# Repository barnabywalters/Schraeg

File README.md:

# Schräg

Schräg is an 8HP multimode filter module for the eurorack format, based off the [Bastl Cinnamon](https://bastl-instruments.com/eurorack/modules/cinnamon).

## Smaller Warning and Disclaimer

As of 2021-03-01, at least one person has reported successfully building the current board revision. However, another builder reported a minor issue with the attenuverter circuits which prevents full-range voltage control over resonance (and limits voltage control over FM). This should be fixable only with component substitutions, we’re working on a fix. More information and updates [in the corresponding lines thread](https://llllllll.co/t/diy-module-release-schrag-bastl-cinnamon-rework/40590).

See the Changelog below for more updates and version-specific fixes.

## Quick links

* [Schematic](Schraeg/Schraeg.pdf)
* [Gerbers](Schraeg/output)
* [BOM](Schraeg/Schraeg%20BOM.csv)
* [Schräg on ModularGrid](https://www.modulargrid.net/e/other-unknown-schraeg)
* [Schräg release and Q&A thread on lines](https://llllllll.co/t/diy-module-release-schrag-bastl-cinnamon-rework/40590)

## Need help assembling your Schräg?

I can’t promise quick responses, but am happy to try to help out!

If you’re **having trouble or need help assembling or troubleshooting** a Schräg, please start a [discussion](https://github.com/barnabywalters/Schraeg/discussions/new).

If you’ve **found a specific error which needs fixing**, please file an [issue](https://github.com/barnabywalters/Schraeg/issues/new).

If you’re not sure which, start a discussion, and we’ll convert it into an issue if we can distill it into a concrete problem.

## Features

Schräg is effectively a repackaged Bastl Cinnamon:

* Multimode filter with independent outputs (2-pole LP, 2-pole HP, 1-pole BP)
* V/oct input
* Self-resonates for use as a sine oscillator
* Input with an attenuator and 5x gain switch
* Two character switches for altering the resonance tracking
* All-SMD construction in a DIY-friendly format, with 0603 handsoldering footprints, all components on the back of the circuit board
* Built mostly using standard and easily-available components

with a few modifications:

* larger 8HP form factor, allowing for a big juicy cutoff knob and larger character and gain switches
* Voltage control over resonance, through an attenuverter
* FM input through an attenuverter, which works as a pitch fine-tune control with nothing patched
* A bi-directional power connector, with polyfuses
* An Interactive BOM (`Schraeg/Output/Interactive BOM.html` once you’ve cloned the repo locally) to aid in part placement
* Schematics and PCB laid out using KiCAD

The additional functionality is achieved with a minimum of extra components, thanks to the two unused VCA cells in the original design.

## License

The schematic, board layout and graphics are released under a cc-by-sa license. [Bastl Instruments](https://bastl-instruments.com/) generously gave their permission for me to release my rework of their module. They’re a cool company. Go check out their work!

## Development

In 2019 I was looking through the [Bastl Cinnamon schematic](https://github.com/bastl-instruments/bastlSchematics/blob/master/CINNAMON_V1.2.pdf) and realised that it only uses two of the four available V2164D VCA cells.

At the time I needed PCB layout practise (and a filter module for my DIY eurorack!), so I ended up prototyping and building an 8HP version of cinnamon for myself which uses the two spare cells to implement voltage control over resonance, as well as a few other little additions listed above.

I called it “Schräg” because of both the angled panel design, the weird sounds possible with Bastl’s cool distortion circuits, and the strange way KiCAD mangled the panel graphics.

A bit more than a year after building the first Schräg, I finally got around to fixing the various small issues with the first board revision, and asking Bastl if they were okay with me open-sourcing the project. They were, and here we are.

## Changelog

### v0.2.1

* Fixed the LM4040 schematic symbols and PCB traces (#2)

### v0.2

* First version released to the public.
* These boards have an issue with the LM4040 orientation (see #2). Depending on the specific LM4040s, it may not cause any problems, but if building from scratch it’s best to install them correctly the first time. To fix it, solder the LM4040s at an angle so that pin 2 (NC) gets connected to pin 3 (5V Ref or GND, depending on the LM4040)

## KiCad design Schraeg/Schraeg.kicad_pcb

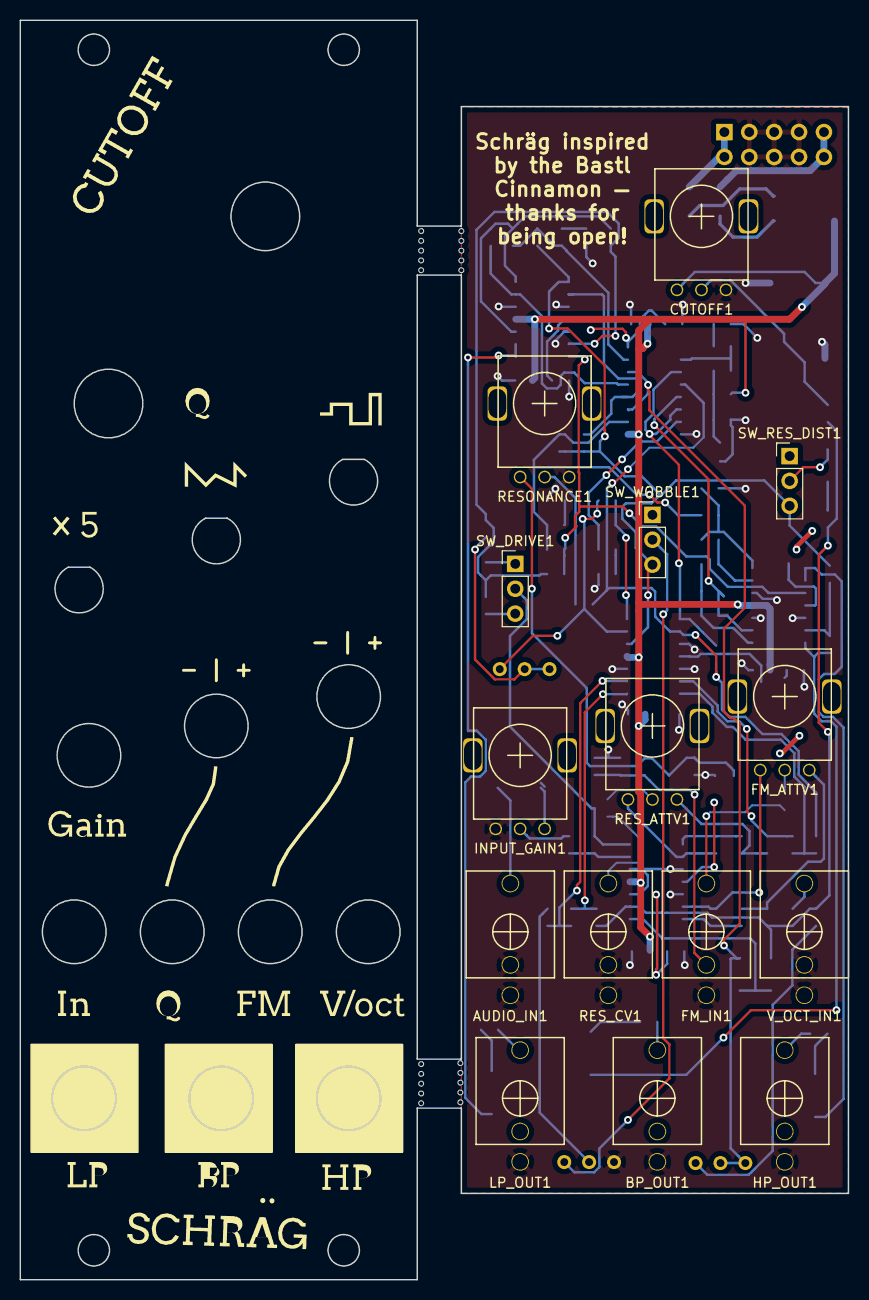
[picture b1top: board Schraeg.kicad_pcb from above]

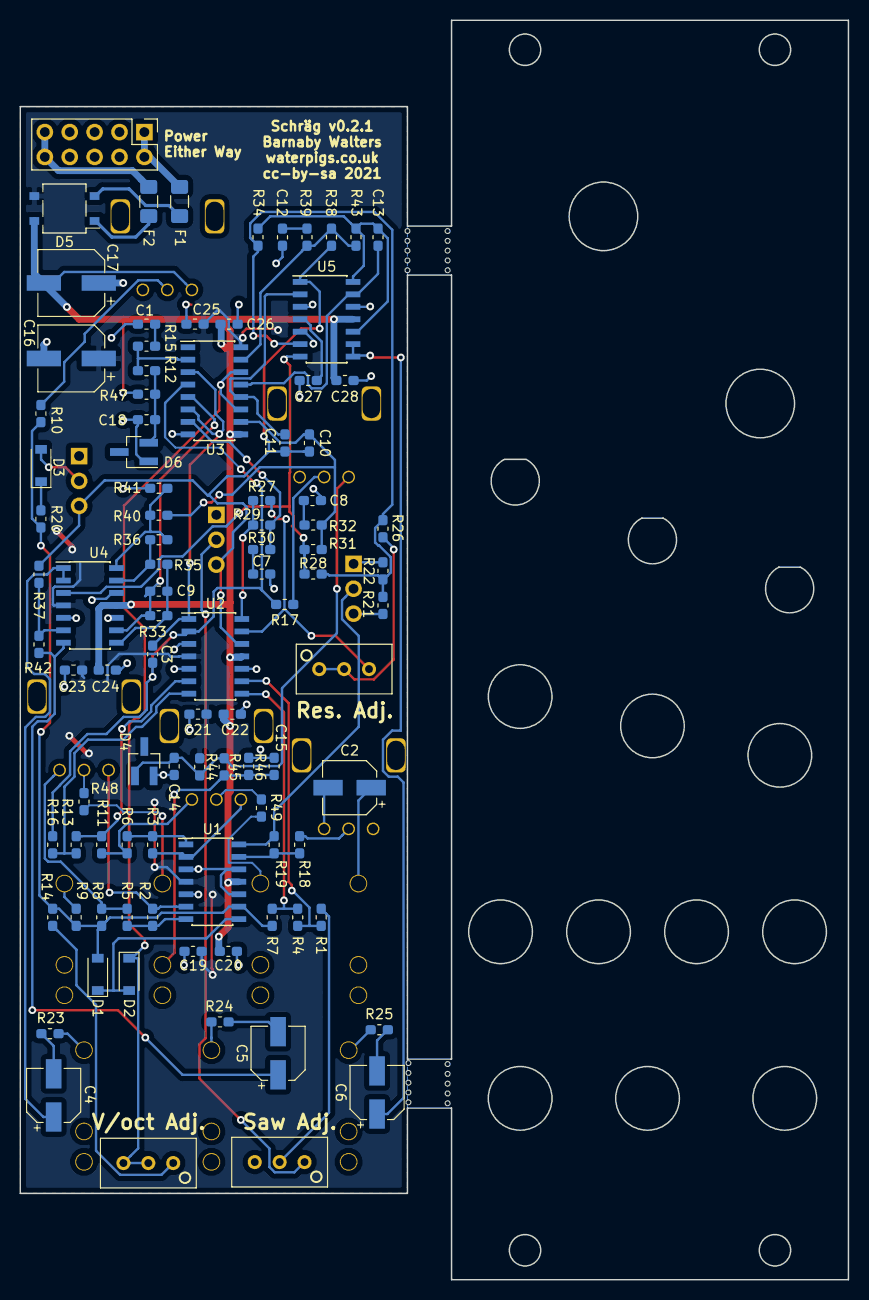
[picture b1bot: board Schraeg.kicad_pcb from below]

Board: 2 copper layers, 84.5 x 128.5 mm, 116 parts (94 on the bottom side), 75 nets.

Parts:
AUDIO_IN1: PJ301M-12
BP_OUT1: PJ301M-12
C1, C7, C8, C12: 560pF; C_0603_1608Metric_Pad1.05x0.95mm_HandSolder
C2, C4, C5, C6: 10uF; CP_Elec_5x4.5
C3, C9: 100pF; C_0603_1608Metric_Pad1.05x0.95mm_HandSolder
C10, C11, C13: 220pF; C_0603_1608Metric_Pad1.05x0.95mm_HandSolder
C14, C15, C18: 220n; C_0603_1608Metric_Pad1.05x0.95mm_HandSolder
C16, C17: 22uF; CP_Elec_6.3x5.4
C19, C20, C21, C22, C23, C24, C25, C26, C27, C28: 100n; C_0603_1608Metric_Pad1.05x0.95mm_HandSolder
CUTOFF1: 100k; Alpha9mmPot
D1, D2: D_Small; D_SOD-123
D3: 5V; D_SOD-123
D4, D6: LM4040DBZ-5; SOT-23_Handsoldering
D5: MB2S; TO-269AA
F1, F2: Polyfuse; Fuse_1206_3216Metric_Pad1.42x1.75mm_HandSolder
FM_ATTV1: 100k; Alpha9mmPot
FM_IN1: PJ301M-12
HP_OUT1: PJ301M-12
INPUT_GAIN1: 100k; Alpha9mmPot
LP_OUT1: PJ301M-12
MOUSEBITE1mm, MOUSEBITE1mm#2, MOUSEBITE1mm#3, MOUSEBITE1mm#4: VAL**; MOUSEBITE1mm
PWR_IN1: EURO_PWR_2x5; PinHeader_2x05_P2.54mm_Vertical
R1, R2, R3, R4, R5, R6, R7, R8, R9, R10, R11, R12, R13, R16, R17, R20: 100k; R_0603_1608Metric_Pad1.05x0.95mm_HandSolder
R14, R40: 15K; R_0603_1608Metric_Pad1.05x0.95mm_HandSolder
R15, R30, R32, R39: 470R; R_0603_1608Metric_Pad1.05x0.95mm_HandSolder
R18: 22k; R_0603_1608Metric_Pad1.05x0.95mm_HandSolder
R19, R22: 47k; R_0603_1608Metric_Pad1.05x0.95mm_HandSolder
R21: 10k; R_0603_1608Metric_Pad1.05x0.95mm_HandSolder
R23, R24, R25: 1K; R_0603_1608Metric_Pad1.05x0.95mm_HandSolder
R26: 330K; R_0603_1608Metric_Pad1.05x0.95mm_HandSolder
R27, R28, R29, R31, R33, R34, R35, R36, R38: 33k; R_0603_1608Metric_Pad1.05x0.95mm_HandSolder
R37, R42, R45, R48, R49: 100K; R_0603_1608Metric_Pad1.05x0.95mm_HandSolder
R41: 1.5K; R_0603_1608Metric_Pad1.05x0.95mm_HandSolder
R43: 470K; R_0603_1608Metric_Pad1.05x0.95mm_HandSolder
R44, R47: 6.8K; R_0603_1608Metric_Pad1.05x0.95mm_HandSolder
R46: 3.3K; R_0603_1608Metric_Pad1.05x0.95mm_HandSolder
RESONANCE1: 100k; Alpha9mmPot
RES_ADJ1: 250K; Potentiometer_Bourns_3296W_Vertical
RES_ATTV1: 100k; Alpha9mmPot
RES_CV1: PJ301M-12
RV_SAW_OCTAVE1: 100k; Potentiometer_Bourns_3296W_Vertical
Ref**: Val**; Schraeg Panel Graphics Inkscape
Ref**#2: Val**; Schraeg Panel Graphics Inkscape
SW_DRIVE1: SW_SPDT; PinHeader_1x03_P2.54mm_Vertical
SW_RES_DIST1: SW_SPDT; PinHeader_1x03_P2.54mm_Vertical
SW_WOBBLE1: SW_SPDT; PinHeader_1x03_P2.54mm_Vertical
U1, U2, U4, U5: TL074; SOIC-14_3.9x8.7mm_P1.27mm
U3: V2164; SOIC-16_3.9x9.9mm_P1.27mm
V_OCT_IN1: PJ301M-12
V_OCT_SCALE1: 5K; Potentiometer_Bourns_3296W_Vertical
svg2mod: G***; Schraeg Panel Graphics Inkscape

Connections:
0.16V_REF: C15.1, FM_IN1.2, R45.2, R46.1
5V_REF: C14.1, D4.1, R44.2, R45.1, RESONANCE1.1
+12V: C16.1, C19.1, C21.1, C23.1, C25.1, C27.1, D5.3, R44.1, U1.4, U2.4, U3.16, U4.4, U5.4
-5V_REF: C18.1, D6.2, R12.2, R47.2
-12V: C17.2, C20.2, C22.2, C24.2, C26.2, C28.2, CUTOFF1.1, D5.4, R47.1, U1.11, U2.11, U3.9, U4.11, U5.11
/Filter Core/AUDIO_IN: R21.1, R22.1, R26.2, R28.2, R34.2, U5.6
/Filter Core/BP_OUT: C5.1, R42.1, U4.7
/Filter Core/FREQ_CV: D2.1, U3.11, U3.14, V_OCT_SCALE1.2, V_OCT_SCALE1.3
/Filter Core/HP_OUT: C4.1, U4.1, U4.2
/Filter Core/LP_OUT: C6.1, U5.8, U5.9
/Filter Core/RES_CV: C3.1, U2.1, U3.3, U3.6
/Filter Core/RES_MOD: C10.1, C11.1, R37.2, R38.2, SW_RES_DIST1.3, SW_WOBBLE1.3, U2.12, U5.1
GND: AUDIO_IN1.1, AUDIO_IN1.2, BP_OUT1.1, C1.2, C7.2, C8.2, C12.2, C14.2, C15.2, C16.2, C17.1, C18.2, C19.2, C20.1, C21.2, C22.1, C23.2, C24.1, C25.2, C26.1, C27.2, C28.1, CUTOFF1.3, D4.2, D6.1, FM_IN1.1, HP_OUT1.1, INPUT_GAIN1.1, LP_OUT1.1, PWR_IN1.3, PWR_IN1.4, PWR_IN1.5, PWR_IN1.6, PWR_IN1.7, PWR_IN1.8, R41.1, R46.2, RESONANCE1.3, RES_CV1.1, RES_CV1.2, RV_SAW_OCTAVE1.3, U1.3, U1.5, U1.10, U1.12, U2.3, U2.5, U2.10, U3.8, U4.5, U4.10, U4.12, U5.3, U5.5, U5.12, V_OCT_IN1.1, V_OCT_IN1.2
unnamed: AUDIO_IN1.3, C2.1
unnamed: BP_OUT1.3, R24.1
unnamed: C1.1, R15.1
unnamed: C2.2, INPUT_GAIN1.3
unnamed: C3.2, R16.1, R17.1, U2.2, U3.4
unnamed: C4.2, R23.2
unnamed: C5.2, R24.2
unnamed: C6.2, R25.2
unnamed: C7.1, R30.1
unnamed: C8.1, R32.1
unnamed: C9.1, R33.1, R35.2, U4.8
unnamed: C9.2, R33.2, U3.5, U4.9
unnamed: C10.2, R31.1, R32.2, R40.2, U3.10
unnamed: C11.2, U3.12, U5.2
unnamed: C12.1, R39.1
unnamed: C13.1, R34.1, R43.1, U5.10, U5.14
unnamed: C13.2, U3.13, U5.13
unnamed: CUTOFF1.2, R10.2
unnamed: D1.1, D2.2, U1.8
unnamed: D1.2, R7.1, R8.1, R9.1, R10.1, R14.2, R20.1, U1.9
unnamed: D3.1, R20.2
unnamed: D3.2, SW_RES_DIST1.2
unnamed: D5.1, F2.1
unnamed: D5.2, F1.1
unnamed: F1.2, PWR_IN1.1, PWR_IN1.2
unnamed: F2.2, PWR_IN1.9, PWR_IN1.10
unnamed: FM_ATTV1.1, R2.2, U1.6
unnamed: FM_ATTV1.2, R48.2
unnamed: FM_ATTV1.3, R5.1, R8.2
unnamed: FM_IN1.3, R48.1
unnamed: HP_OUT1.3, R23.1
unnamed: INPUT_GAIN1.2, R18.2
unnamed: LP_OUT1.3, R25.1
unnamed: R1.1, R4.2, U2.9
unnamed: R1.2, RV_SAW_OCTAVE1.2
unnamed: R2.1, R5.2, U1.7
unnamed: R3.1, R6.2, U1.1
unnamed: R3.2, RES_ATTV1.1, U1.2
unnamed: R4.1, R7.2, U2.8
unnamed: R9.2, V_OCT_IN1.3
unnamed: R11.1, R13.2, U2.6
unnamed: R6.1, R11.2, RES_ATTV1.3
unnamed: R12.1, R15.2, U3.2
unnamed: R13.1, R16.2, U2.7
unnamed: R14.1, V_OCT_SCALE1.1
unnamed: R17.2, RESONANCE1.2
unnamed: R18.1, R19.2, U1.13
unnamed: R19.1, SW_DRIVE1.2, U1.14
unnamed: R21.2, SW_DRIVE1.3
unnamed: R22.2, SW_DRIVE1.1
unnamed: R26.1, RES_ADJ1.1, RES_ADJ1.2
unnamed: R27.1, R29.2, U2.14
unnamed: R27.2, RES_ADJ1.3, U2.13
unnamed: R28.1, R31.2, U4.3, U5.7
unnamed: R29.1, R30.2, U3.7
unnamed: R35.1, R36.2, U4.13
unnamed: R36.1, R40.1, R41.2, U4.14
unnamed: R37.1, R42.2, U4.6
unnamed: R38.1, R39.2, R43.2, U3.15
unnamed: R49.1, RES_ATTV1.2
unnamed: R49.2, RES_CV1.3
unnamed: RV_SAW_OCTAVE1.1, SW_WOBBLE1.2

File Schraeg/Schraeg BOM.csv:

Reference, Quantity, Value, Footprint, Datasheet,Notes
AUDIO_IN1 BP_OUT1 FM_IN1 HP_OUT1 LP_OUT1 RES_CV1 V_OCT_IN1,7,PJ301M-12,Eurocad:PJ301M-12,,
C1 C12 C7 C8,4,560pF,Capacitor_SMD:C_0603_1608Metric_Pad1.05x0.95mm_HandSolder,~,
C10 C11 C13,3,220pF,Capacitor_SMD:C_0603_1608Metric_Pad1.05x0.95mm_HandSolder,~,
C14 C15 C18,3,220n,Capacitor_SMD:C_0603_1608Metric_Pad1.05x0.95mm_HandSolder,~,
C16 C17,2,22uF,Capacitor_SMD:CP_Elec_6.3x5.4,~,
C19 C20 C21 C22 C23 C24 C25 C26 C27 C28,10,100n,Capacitor_SMD:C_0603_1608Metric_Pad1.05x0.95mm_HandSolder,~,
C2 C4 C5 C6,4,10uF,Capacitor_SMD:CP_Elec_5x4.5,~,
C3 C9,2,100pF,Capacitor_SMD:C_0603_1608Metric_Pad1.05x0.95mm_HandSolder,~,
D1 D2,2,1N4148,Diode_SMD:D_SOD-123,~,
D3,1,5V,Diode_SMD:D_SOD-123,~,5V Zener diode
D5,1,MB2S,Package_TO_SOT_SMD:TO-269AA,http://www.vishay.com/docs/88661/mb2s.pdf,
D4 D6,2,LM4040DCK-5,Package_TO_SOT_SMD:SOT-23_Handsoldering,http://www.ti.com/lit/ds/symlink/lm4040-n.pdf,
F1 F2,2,Polyfuse,Fuse:Fuse_1206_3216Metric_Pad1.42x1.75mm_HandSolder,~,"PPTC fuse of your choice, e.g. 1206L012WR"
CUTOFF1 FM_ATTV1 INPUT_GAIN1 RESONANCE1 RES_ATTV1,5,100k,Eurocad:Alpha9mmPot,~,Any 100k 9mm pot should work
PWR_IN1,1,EURO_PWR_2x5,Connector_PinHeader_2.54mm:PinHeader_2x05_P2.54mm_Vertical,,
R14 R40,2,15K,Resistor_SMD:R_0603_1608Metric_Pad1.05x0.95mm_HandSolder,~,
R15 R30 R32 R39,4,470R,Resistor_SMD:R_0603_1608Metric_Pad1.05x0.95mm_HandSolder,~,
R18,1,22k,Resistor_SMD:R_0603_1608Metric_Pad1.05x0.95mm_HandSolder,~,
R19 R22,2,47k,Resistor_SMD:R_0603_1608Metric_Pad1.05x0.95mm_HandSolder,~,
R21,1,10k,Resistor_SMD:R_0603_1608Metric_Pad1.05x0.95mm_HandSolder,~,
R23 R24 R25,3,1K,Resistor_SMD:R_0603_1608Metric_Pad1.05x0.95mm_HandSolder,~,
R26,1,330K,Resistor_SMD:R_0603_1608Metric_Pad1.05x0.95mm_HandSolder,~,
R27 R28 R29 R31 R33 R34 R35 R36 R38,9,33k,Resistor_SMD:R_0603_1608Metric_Pad1.05x0.95mm_HandSolder,~,
R1 R10 R11 R12 R13 R16 R17 R2 R20 R3 R4 R5 R6 R7 R8 R9,16,100k,Resistor_SMD:R_0603_1608Metric_Pad1.05x0.95mm_HandSolder,~,
R41,1,1.5K,Resistor_SMD:R_0603_1608Metric_Pad1.05x0.95mm_HandSolder,~,
R43,1,470K,Resistor_SMD:R_0603_1608Metric_Pad1.05x0.95mm_HandSolder,~,
R46,1,3.3K,Resistor_SMD:R_0603_1608Metric_Pad1.05x0.95mm_HandSolder,~,
R44 R47,2,6.8K,Resistor_SMD:R_0603_1608Metric_Pad1.05x0.95mm_HandSolder,~,
R37 R42 R45 R48 R49,5,100K,Resistor_SMD:R_0603_1608Metric_Pad1.05x0.95mm_HandSolder,~,
RES_ADJ1,1,250K,Potentiometer_THT:Potentiometer_Bourns_3296W_Vertical,~,
RV_SAW_OCTAVE1,1,100k,Potentiometer_THT:Potentiometer_Bourns_3296W_Vertical,~,
SW_DRIVE1 SW_RES_DIST1 SW_WOBBLE1,3,SW_SPDT,Connector_PinHeader_2.54mm:PinHeader_1x03_P2.54mm_Vertical,~,SPDT switches with 0.1” pin spacing. These Dailywells from Thonk work: https://www.thonk.co.uk/shop/sub-mini-toggle-switches/
U1 U2 U4 U5,4,TL074,Package_SO:SOIC-14_3.9x8.7mm_P1.27mm,http://www.ti.com/lit/ds/symlink/tl071.pdf,
U3,1,V2164,Package_SO:SOIC-16_3.9x9.9mm_P1.27mm,,
V_OCT_SCALE1,1,5K,Potentiometer_THT:Potentiometer_Bourns_3296W_Vertical,~,

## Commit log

2021-01-15 Initial commit
    2019 edition board with fixed attenuverter input resistors, voltage
    reference footprints.
2021-01-15 Finished v0.2
    * Flipped switches
    * Enlarged switch holes
    * Enlarged and enovaled pot support holes
    * Reduced jack socket hole sizes
    * Improved component and component reference locations
    Archived v0.1 (previously know as the 2019 edition) and
2021-01-18 Renamed some files
2021-01-18 Removed photos from repo
2021-01-18 Added README, License, BOM
2021-01-18 Fixed links, image size
2021-01-18 Attempted to fix more links
2021-01-18 Percent-encoded spaces in relative link filenames
2021-01-18 Moved link to interactive BOM to features section
2021-01-18 Added a modulargrid link
2021-01-18 Finished off Development section:
2021-01-18 Update README.md
    Mentioned that the boards are laid out using KiCAD
2021-01-18 Update README.md
    Corrected gain spec
2021-01-27 Added 2019 edition build guide, photos
2021-01-27 Corrected 2019 edition build guide image link
2021-03-01 Reduced size and severity of disclaimer
2021-05-28 Fixed LM4040 symbols and PCB layout. Fixes #2
2021-05-28 Updated board version reference
2021-05-28 Added changelog, fix guide for #2
2022-01-21 Added lines to quick link, added guidance on startign discussions/issues

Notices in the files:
Schraeg/Schraeg.kicad_pcb:
cc-by-sa 2021
